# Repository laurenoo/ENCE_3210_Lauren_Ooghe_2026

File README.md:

# ENCE_3210_Lauren_Ooghe_2026

Lab 1 - Q7 --> Used ChatGPT to figure out how to attack the problem. Learned different ways to execute the code, and decided the best way was to create functions to invoke to keep the code semi-clean inside of the void loop. Did not copy/paste, just mimicked layout of different versions. Also learned how to use switch() function with cases. This helps workload so I don't have to write as many if statements and is more versatile and not hard-coded. Willing to explain method of thinking and understanding of the code.

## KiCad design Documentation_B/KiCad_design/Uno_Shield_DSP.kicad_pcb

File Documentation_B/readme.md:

**** SEE PCB_V1 FOLDER FOR COMPLETED PROJECT CONTENTS ****

4-bit DAC was created on the breadboard to simulate output response to a given digital input. 
The ramp.ino file was created using ChatGPT due to limited time and understanding of the design. I would like to try to build a 10-bit DAC and 
measure the output to get a smooth continuous output without clipping. In order to prevent clipping, I need to figure out the appropriate resistor
values needed for the DC offset on the op-amp.

KiCad files were added. The layout is determined, but also subject to change due to dependance on tracing practices.

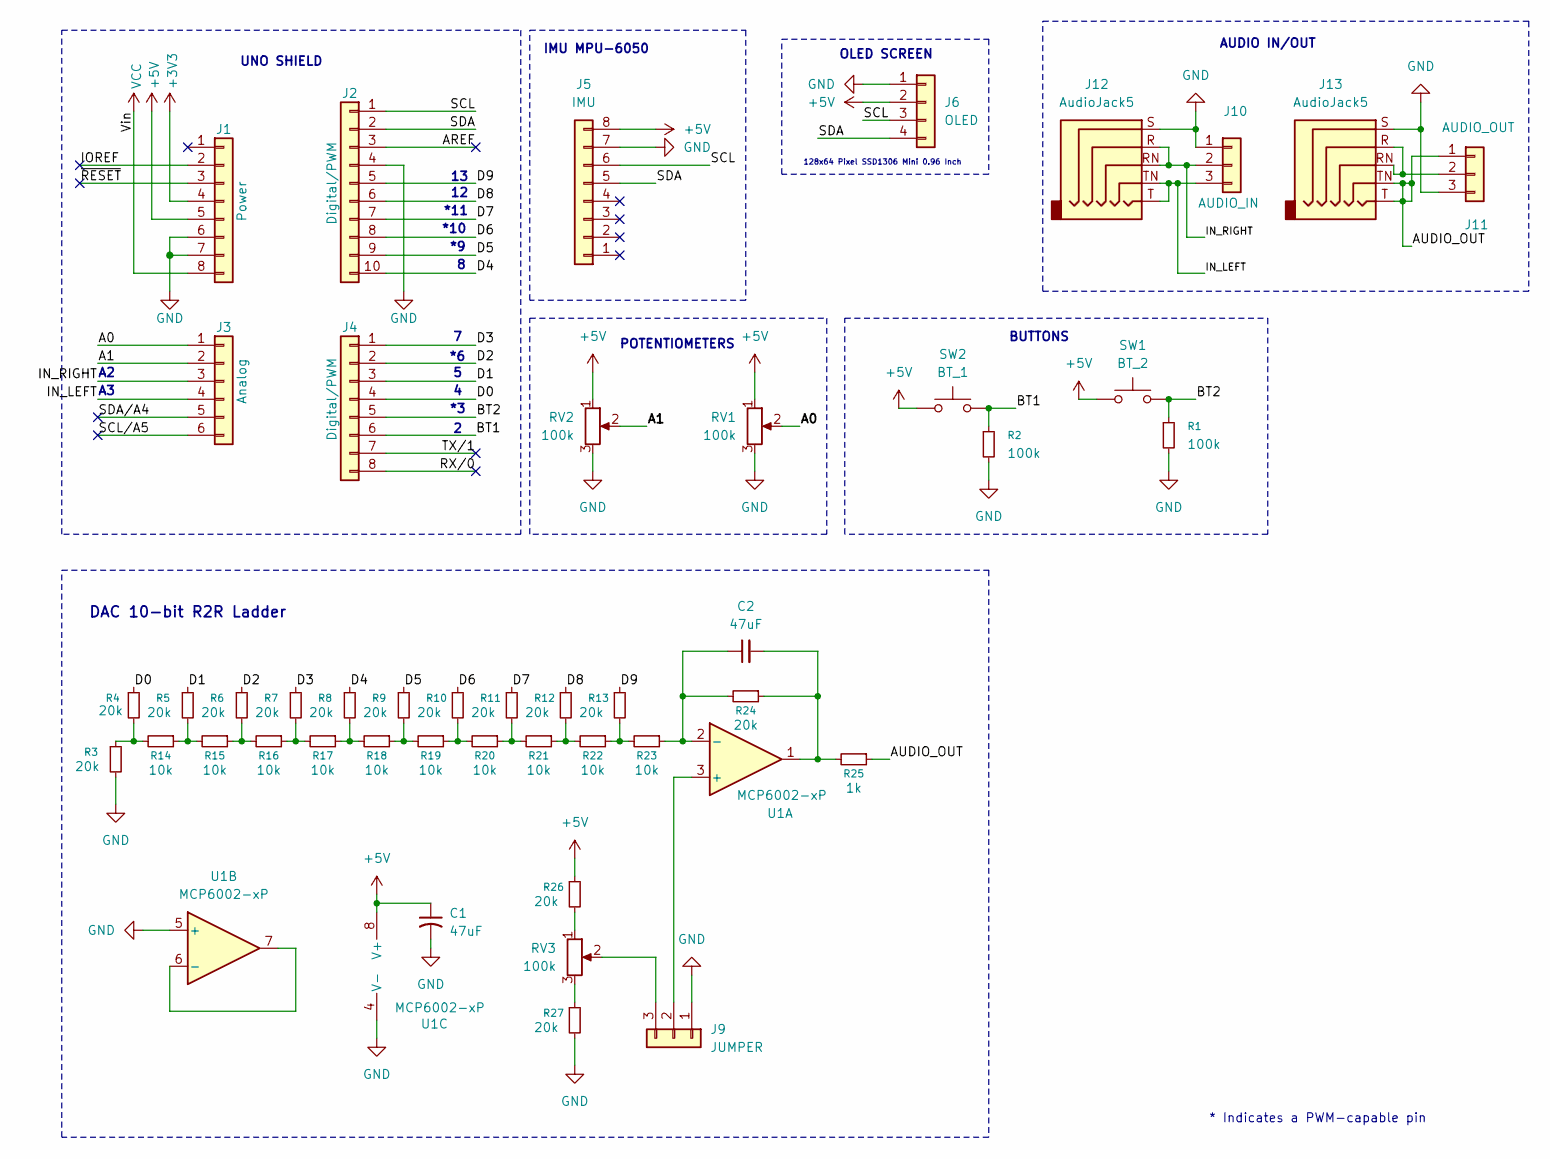
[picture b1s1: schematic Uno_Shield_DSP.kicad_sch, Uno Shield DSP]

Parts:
C1: 47uF; CP_Radial_D8.0mm_P2.50mm
C2: 47uF; C_Disc_D4.7mm_W2.5mm_P5.00mm
J1: Power; PinSocket_1x08_P2.54mm_Vertical
J2: Digital/PWM; PinSocket_1x10_P2.54mm_Vertical
J3: Analog; PinSocket_1x06_P2.54mm_Vertical
J4: Digital/PWM; PinSocket_1x08_P2.54mm_Vertical
J5: IMU; PinSocket_1x08_P2.54mm_Vertical
J6: OLED; PinSocket_1x04_P2.54mm_Vertical
J9: JUMPER; PinHeader_1x03_P2.54mm_Vertical
J10: AUDIO_IN; PinHeader_1x03_P2.54mm_Vertical
J11: AUDIO_OUT; PinHeader_1x03_P2.54mm_Vertical
J12, J13: AudioJack5; Jack_3.5mm_CUI_SJ1-3525N_Horizontal
R1, R2: 100k; R_Axial_DIN0309_L9.0mm_D3.2mm_P2.54mm_Vertical
R3, R4, R5, R6, R7, R8, R9, R10, R11, R12, R13, R24, R26, R27: 20k; R_Axial_DIN0309_L9.0mm_D3.2mm_P2.54mm_Vertical
R14, R15, R16, R17, R18, R19, R20, R21, R22, R23: 10k; R_Axial_DIN0309_L9.0mm_D3.2mm_P2.54mm_Vertical
R25: 1k; R_Axial_DIN0309_L9.0mm_D3.2mm_P2.54mm_Vertical
RV1, RV2, RV3: 100k; Potentiometer_Bourns_3386P_Vertical
SW1: BT_2; SW_PUSH_6mm
SW2: BT_1; SW_PUSH_6mm
U1: MCP6002-xP; DIP-8_W7.62mm_Socket_LongPads

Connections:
+3V3: J1.4
+5V: C1.1, J1.5, J5.8, J6.2, R26.1, RV1.1, RV2.1, SW1.1, SW2.1, U1.8 (V+)
/A0: J3.1, RV1.2
/A1: J3.2, RV2.2
/AREF: J2.3
/AUDIO_OUT: J11.1, J13.T, J13.TN, R25.1
/BT1: J4.6, R2.1, SW2.2
/BT2: J4.5, R1.1, SW1.2
/D0: J4.4, R4.1
/D1: J4.3, R5.1
/D2: J4.2, R6.1
/D3: J4.1, R7.1
/D4: J2.10, R8.1
/D5: J2.9, R9.1
/D6: J2.8, R10.1
/D7: J2.7, R11.1
/D8: J2.6, R12.1
/D9: J2.5, R13.1
/IN_LEFT: J3.4, J10.3, J12.T, J12.TN
/IN_RIGHT: J3.3, J10.2, J12.R, J12.RN
/IOREF: J1.2
/RX/0: J4.8
/SCL: J2.1, J5.6, J6.3
/SCL/A5: J3.6
/SDA: J2.2, J5.5, J6.4
/SDA/A4: J3.5
/TX/1: J4.7
/~RESET: J1.3
GND: C1.2, J1.6, J1.7, J2.4, J5.7, J6.1, J9.1, J10.1, J11.3, J12.S, J13.S, R1.2, R2.2, R3.2, R27.2, RV1.3, RV2.3, U1.4 (V-), U1.5 (+)
unnamed: C2.2, R24.1, R25.2, U1.1
unnamed: J9.2, U1.3 (+)
unnamed: J9.3, RV3.2
unnamed: J11.2, J13.R, J13.RN
unnamed: R10.2, R19.1, R20.2
unnamed: R11.2, R20.1, R21.2
unnamed: R12.2, R21.1, R22.2
unnamed: R13.2, R22.1, R23.2
unnamed: R5.2, R14.1, R15.2
unnamed: R3.1, R4.2, R14.2
unnamed: R6.2, R15.1, R16.2
unnamed: R7.2, R16.1, R17.2
unnamed: R8.2, R17.1, R18.2
unnamed: R9.2, R18.1, R19.2
unnamed: R26.2, RV3.1
unnamed: R27.1, RV3.3
unnamed: C2.1, R23.1, R24.2, U1.2 (-)
unnamed: U1.6 (-), U1.7
VCC: J1.8

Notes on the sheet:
AUDIO IN/OUT
DAC 10-bit R2R Ladder
IMU MPU-6050
*11
*10
POTENTIOMETERS
128x64 Pixel SSD1306 Mini 0.96 Inch
* Indicates a PWM-capable pin
OLED SCREEN
BUTTONS
UNO SHIELD

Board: 2 copper layers, 46 parts (0 on the bottom side), 39 nets, no tracks yet.

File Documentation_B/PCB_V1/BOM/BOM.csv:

"Id";"Designator";"Footprint";"Quantity";"Designation";"Supplier and ref";
1;"J1";"PinSocket_1x08_P2.54mm_Vertical";1;"Power";;;
2;"J3";"PinSocket_1x06_P2.54mm_Vertical";1;"Analog";;;
3;"J2";"PinSocket_1x10_P2.54mm_Vertical";1;"Digital/PWM";;;
4;"J4";"PinSocket_1x08_P2.54mm_Vertical";1;"Digital/PWM";;;
5;"R9,R10,R7,R5,R13,R12,R8,R6,R4,R11,R3";"R_Axial_DIN0309_L9.0mm_D3.2mm_P2.54mm_Vertical";11;"20k";;;
6;"SW1";"SW_PUSH_6mm";1;"BT_2";;;
7;"R17,R14,R20,R16,R21,R22,R18,R19,R15";"R_Axial_DIN0309_L9.0mm_D3.2mm_P2.54mm_Vertical";9;"10k";;;
8;"C2";"C_Disc_D4.7mm_W2.5mm_P5.00mm";1;"100pF";;;
9;"U1";"DIP-8_W7.62mm_Socket_LongPads";1;"MCP6002-xP";;;
10;"J13,J12";"Jack_3.5mm_CUI_SJ1-3525N_Horizontal";2;"AudioJack5";;;
11;"C1";"CP_Radial_D8.0mm_P2.50mm";1;"47uF";;;
12;"RV3,RV1,RV2";"Potentiometer_Bourns_3386P_Vertical";3;"100k";;;
13;"R26,R27,R24";"R_Axial_DIN0204_L3.6mm_D1.6mm_P7.62mm_Horizontal";3;"20k";;;
14;"J5";"PinSocket_1x08_P2.54mm_Vertical";1;"IMU";;;
15;"R1,R2";"R_Axial_DIN0309_L9.0mm_D3.2mm_P2.54mm_Vertical";2;"100k";;;
16;"J6";"PinSocket_1x04_P2.54mm_Vertical";1;"OLED";;;
17;"SW2";"SW_PUSH_6mm";1;"BT_1";;;
18;"R23";"R_Axial_DIN0204_L3.6mm_D1.6mm_P7.62mm_Horizontal";1;"10k";;;
19;"R25";"R_Axial_DIN0204_L3.6mm_D1.6mm_P7.62mm_Horizontal";1;"1k";;;
20;"J9";"PinHeader_1x03_P2.54mm_Vertical";1;"JUMPER";;;
21;"J11";"PinHeader_1x03_P2.54mm_Vertical";1;"AUDIO_OUT";;;
22;"J10";"PinHeader_1x03_P2.54mm_Vertical";1;"AUDIO_IN";;;

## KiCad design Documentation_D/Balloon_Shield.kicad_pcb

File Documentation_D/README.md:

# Weather Balloon Arduino Shield Redesign - PHASE 2
This is Phase 2 of the Weather Balloon Arduino Shield redesign. 
The goal was to redesign the system due to unavailable parts with a budget constraint of $147 and a weight constraint of 200g.
In this repository, all of the PCB design documents are listed. Phase 1 of this design can be found in the BalloonDesign/Phase1 folder inside of this repository. Below, you'll find the block diagram of the system with cost and weight estimates.
## BLOCK DIAGRAM

## ESTIMATED WEIGHT

## ESTIMATED COST

### All PCB design materials are located within this repository.
Pictures of the design can be found in the Docs folder while the gerber files can be found in the gerber folder.

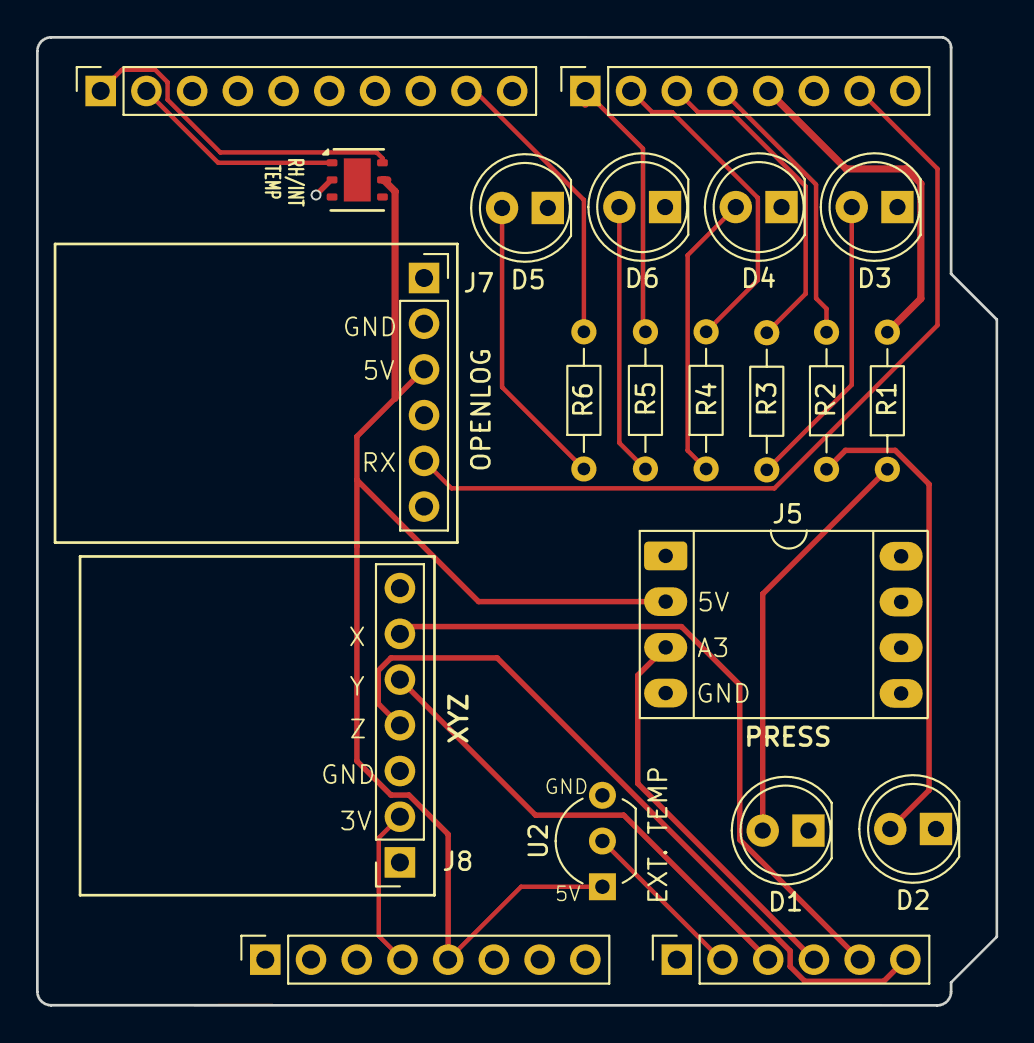
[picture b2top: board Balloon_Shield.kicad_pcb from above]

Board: 2 copper layers, 53.3 x 53.8 mm, 21 parts (0 on the bottom side), 23 nets.

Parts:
D1, D2, D3, D4, D5, D6: LED; LED_D5.0mm
HDC1080: HDC1080; Texas_PWSON-N6
J1: Power; PinSocket_1x08_P2.54mm_Vertical
J2: Digital/PWM; PinSocket_1x10_P2.54mm_Vertical
J3: Analog; PinSocket_1x06_P2.54mm_Vertical
J4: Digital/PWM; PinSocket_1x08_P2.54mm_Vertical
J5: Conn_01x04; DIP-8_W7.62mm_Socket_LongPads
J7: Conn_01x06; PinSocket_1x06_P2.54mm_Vertical
J8: Conn_01x07; PinSocket_1x07_P2.54mm_Vertical
R1, R2, R3, R4, R5, R6: R; R_Axial_DIN0204_L3.6mm_D1.6mm_P7.62mm_Horizontal
U2: EXT TEMP; TO-92_Inline_Wide

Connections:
+3V3: J1.4, J8.2
+5V: HDC1080.5 (VCC), J1.5, J5.2, J7.3, U2.1 (V+)
/3: J4.5, R1.2
/4: J4.4, R2.2
/5: J4.3, R3.2
/6: J4.2, R4.2
/7: J4.1, R5.2
/9: J2.9, R6.2
/A1: J3.2, U2.2 (Signal)
/A2: J3.3, J8.5
/A3: J3.4, J5.3
/A4: J3.5, J8.6
/A5: J3.6, J8.4
/SCL: HDC1080.6 (SCL), J2.1
/SDA: HDC1080.1 (SDA), J2.2
/TX: J4.7, J7.5
GND: D1.1 (K), D2.1 (K), D3.1 (K), D4.1 (K), D5.1 (K), D6.1 (K), HDC1080.2 (GND), J1.6, J1.7, J2.4, J5.4, J7.2, J8.3, U2.3 (GND)
unnamed: D1.2 (A), R1.1
unnamed: D2.2 (A), R2.1
unnamed: D3.2 (A), R3.1
unnamed: D4.2 (A), R4.1
unnamed: D5.2 (A), R6.1
unnamed: D6.2 (A), R5.1

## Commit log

2026-01-09 Create Lab1
2026-01-09 Implement quadratic function to calculate roots
2026-01-09 Calculate twice the square of numbers
2026-01-09 Cosine of integer degrees
2026-01-09 Find second highest integer
2026-01-09 Count occurrences of R, G, and B in an array
    Fix loop condition to prevent out-of-bounds access.
2026-01-11 Find cosine from 0 to 360º and save in array
2026-01-11 Rename Q1 to Q1 - C code
2026-01-11 Enhance code readability with comments
    Added comments for clarity and understanding of the code.
2026-01-11 Rename Q3 to Q3 - C code
2026-01-11 Find second max number
    This program searches for the second maximum number in a global array of 50 integers and prints the result.
2026-01-11 R, G, B occurrences
    Updated the code to count occurrences of R, G, and B in an array and control LEDs accordingly.
2026-01-11 Add Lab1 for C exercise in class
2026-01-11 Remove return statement from loop function
    Removed unnecessary return statement from loop function.
2026-01-11 Implement pattern detection with LED indicators
    This program detects a specified pattern in an array and controls LEDs based on the detection. It counts the occurrences of the pattern and indicates the result through green and red LEDs.
2026-01-11 Implement LED control with button press
2026-01-11 Added comments
    Refactor LED control logic to improve readability.
2026-01-13 Update LED sequence and button press handling
2026-01-13 Update header comment for Lab 1 Q6
2026-01-13 Clarify toggleTime comment in Q6
    Updated comment for clarity on toggleTime usage.
2026-01-13 improve comments in Q6
2026-01-14 Refactor LED control logic and update button pin
2026-01-14 Add LED calculator functionality with button input
    This code implements an LED calculator that performs addition, subtraction, and multiplication using button inputs. It includes debouncing for button presses and displays the results using LEDs.
2026-01-14 Added comments
2026-01-14 Update README with Lab 1 Q7 details
    Coding strategies
2026-01-16 Add comment about using an interrupt for LEDs
2026-01-16 update description
2026-01-19 Implement quadratic formula calculation in C
2026-01-19 Calculate sum and average
2026-01-27 Update README with LAB 3 block diagram
    Added a block diagram image for LAB 3 and removed details about LAB 1.
2026-01-30 Fix formatting of timer compare value definitions
2026-02-01 4 bit DAC Circuit
2026-02-01 Add comment to 4-bitDAC file
    Add initial comment referencing the next file
2026-02-01 Add files via upload
    ChatGPT code
2026-02-02 Add ramp.ino to Documentation_B
2026-02-02 Rename IMG_4358.jpeg to 4-bit_DAC_Circuit
2026-02-02 Rename IMG_4359.jpeg to 4-bit_DAC_RampOutput
2026-02-02 Rename Lab3.ino to lab3/interrupt.ino
2026-02-02 Rename README.md to lab3/readme.md
2026-02-02 Add initial readme for 4-bit DAC project
2026-02-02 Add 4-bit DAC design documentation
2026-02-02 Update and rename Documentation_B/4-bit_DAC_RampOutput to Documentation_B/DAC_proto/4-bit_DAC_RampOutput
2026-02-02 Rename Documentation_B/ramp.ino to Documentation_B/DAC_proto/ramp.ino
2026-02-02 Create KiCad
2026-02-02 Rename Uno_Shield_DSP.kicad_sch to no_Shield_DSP.kicad_sch
2026-02-02 Rename no_Shield_DSP.kicad_sch to Uno_Shield_DSP.kicad_sch
2026-02-02 Update STEP file for 10 kΩ Breadboard Trim Potentiometer
2026-02-02 Rename Documentation_B/KiCad_design/ITG-MPU.STEP to Documentation_B/KiCad_design/Components/ITG-MPU.STEP
2026-02-02 Move MountingHole_1.2mm.kicad_mod to new directory
2026-02-02 Add MountingHole_3.2mm.kicad_mod to Arduino directory
2026-02-02 Add OLED TEMU 0.96 in.stp to components directory
2026-02-02 Rename Documentation_B/KiCad_design/screen_dimensions.png to Documentation_B/KiCad_design/Components/screen_dimensions.png
2026-02-02 Update readme with DAC project details and KiCad files
    Added information about KiCad files and DAC design considerations.
2026-02-03 Update 10 kΩ Breadboard Trim Potentiometer file
2026-02-03 Rename Documentation_B/PCB_V1/ITG-MPU.STEP to Documentation_B/PCB_V1/Docs/ITG-MPU.STEP
2026-02-03 Rename Documentation_B/PCB_V1/PCB_3D.png to Documentation_B/PCB_V1/Docs/PCB_3D.png
2026-02-03 Rename Documentation_B/PCB_V1/PCB_BACK.png to Documentation_B/PCB_V1/Docs/PCB_BACK.png
2026-02-03 Rename Documentation_B/PCB_V1/PCB_FRONT.png to Documentation_B/PCB_V1/Docs/PCB_FRONT.png
2026-02-03 Rename Documentation_B/PCB_V1/PCB_LAYOUT.png to Documentation_B/PCB_V1/Docs/PCB_LAYOUT.png
2026-02-03 Rename Documentation_B/PCB_V1/PCB_SCH.png to Documentation_B/PCB_V1/Docs/PCB_SCH.png
2026-02-04 Rename Documentation_B/PCB_V1/gerber/Uno_Shield_DSP.kicad_pcb to Documentation_B/PCB_V1/Uno_Shield_DSP.kicad_pcb
2026-02-27 Rename block_diagram.jpg to Lab_4/Q2_block_diagram.jpg
2026-02-27 Rename IMG_4552.jpeg to batt_charging.jpeg
2026-02-27 Rename Microprocessors.png to Q4_blockdiagram.png
2026-02-27 Update readMe.md with documentation status
2026-03-06 Rename Documentation_C/DAC_ISR_Test.ino to Documentation_C/Test_Codes/DAC_ISR_Test.ino
2026-03-06 Rename Documentation_C/DSP_Shield_Rotating_Menu.ino to Documentation_C/Test_Codes/DSP_Shield_Rotating_Menu.ino
2026-03-06 Add overview and report details to readme.md
2026-03-09 Add readme.md for BalloonDesign Phase 1
2026-03-09 Rename BalloonDesign_Phase1/Balloon Shield Design.pdf to BalloonDesign/Phase1/Balloon Shield Design.pdf
2026-03-13 Update README with Phase 2 redesign details
    Added details about the Weather Balloon Arduino Shield redesign, including goals, block diagram, estimated weight, and cost.
2026-03-13 Update README to include Phase 1 design reference
    Added reference to Phase 1 design documents in README.
2026-03-13 Replace cost image with a new image link
2026-03-13 Rename Documentation_D/gerber/lauren_ooghe_balloon.zip to Documentation_D/gerber/ZIP_FILE/lauren_ooghe_balloon.zip
